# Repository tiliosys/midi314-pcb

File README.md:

midi@3:14 is a home-made electronic keyboard for playing music.

It has been designed with the following requirements:

* Small size, light weight.
* Uniform layout.
* Compatible with any computer hardware (PC, Raspberry Pi, &hellip;) and free software synthesizers.

As a result, midi@3:14 has the following characteristics:

* [Jankó](https://en.wikipedia.org/wiki/Jank%C3%B3_keyboard) layout with 3 rows of 14 keys.
* 5 potentiometers that can be used to change the volume, or any other control value supported by the MIDI standard.
* A USB-MIDI interface.

This repository contains the CAD files of the midi@3:14 keyboard PCB.
They have been initially created with Kicad 5, and migrated to Kicad 6.

Electronic design
-----------------

The keyboard is designed as a switch matrix using the same techniques as a typical mechanical computer keyboard.
The main components are:

* 42 switches from the Cherry MX family,
* 42 diodes to prevent the "ghosting" effect when playing chords,
* 5 potentiometers,
* A microcontroller module, the Arduino-compatible [SparkFun Pro Micro](https://www.sparkfun.com/products/12640),
* A custom printed circuit board (PCB).

For more explanations about making a matrix keyboard, see the blog post
[How to make a keyboard - The matrix](http://blog.komar.be/how-to-make-a-keyboard-the-matrix/)
by Michał Trybus.

In this project, while the actual keyboard is composed of 3 rows with 14 keys per row,
it is electrically organized as a 6&times;7 switch matrix:

PCB layout
----------

The PCB measures about 28.7 cm by 9.1 cm.
It uses two copper layers.
The switches, potentiometers, and the *Pro Micro* module are placed on the top layer; the diodes are placed on the bottom layer.

The following footprints are used:

* Potentiometers: Bourns PTV09A, vertical.
* Switches: Cherry MX 1u, PCB-mounted.
* Diodes: DO-35, horizontal, through-hole, 10.16 mm.
* Pro Micro: DIP-24, width 15.24 mm.

Here is a picture of the PCB, manufactured by a Chinese company called [Elecrow](https://www.elecrow.com).

Bill of materials and cost
--------------------------

Here is the list of parts used in this project, and the additional costs.
I have kept the prices in the currencies that were used when ordering (US dollars and Euros).
Note that these prices were applicable in March 2018.
They are likely to have changed since.

The first line shows that 50 key switches were ordered from WASD while only 42 were needed.
In fact, their unit price was lower when ordering 50 and it turned out to be cheaper.

| Description                                                                                                                 | Reference         | Provider                                                       | Qty | Unit price | Total price |
|:----------------------------------------------------------------------------------------------------------------------------|:------------------|:---------------------------------------------------------------|----:|-----------:|------------:|
| [Cherry MX Red Keyswitch (Linear) PCB Mounted](https://www.wasdkeyboards.com/cherry-mx-red-keyswitch-mx1a-l1nw-linear.html) | MX1A-L1NW         | [WASD](http://www.wasdkeyboards.com)                           |  50 |      $0.75 |      $37.50 |
| [Row 4, Size 1x1 Cherry MX Keycap](https://www.wasdkeyboards.com/row-4-size-1x1-cherry-mx-keycap.html), Beige               | R4-1X1            | [WASD](http://www.wasdkeyboards.com)                           |  23 |      $1.00 |      $23.00 |
| [Row 4, Size 1x1 Cherry MX Keycap](https://www.wasdkeyboards.com/row-4-size-1x1-cherry-mx-keycap.html), Charcoal            | R4-1X1            | [WASD](http://www.wasdkeyboards.com)                           |  18 |      $1.00 |      $18.00 |
| [Row 4, Size 1x1 Cherry MX Keycap](https://www.wasdkeyboards.com/row-4-size-1x1-cherry-mx-keycap.html), Orange              | R4-1X1            | [WASD](http://www.wasdkeyboards.com)                           |   1 |      $1.00 |       $1.00 |
| Keyboard parts, shipping to France                                                                                          |                   | USPS                                                           |   1 |     $23.50 |      $23.50 |
| Printed Circuit Board                                                                                                       |                   | [Elecrow](https://www.elecrow.com)                             |   1 |     $30.47 |      $30.47 |
| Printed Circuit Board, shipping to France                                                                                   |                   | DHL                                                            |   1 |     $20.03 |      $20.03 |
| Printed Circuit Board, customs                                                                                              |                   | DHL                                                            |   1 |    23.00 € |     23.00 € |
| Potentiometer, Bourns PTV09A series, 10 kOhm                                                                                | PTV09A-4225F-B103 | [Farnell](http://fr.farnell.com/)                              |   5 |     0.97 € |      4.85 € |
| Diodes                                                                                                                      | 1N4148            | [Farnell](http://fr.farnell.com/)                              |  50 |    0.682 € |      3.41 € |
| Components, shipping                                                                                                        |                   |                                                                |   1 |     6.90 € |      6.90 € |
| Components, VAT                                                                                                             |                   |                                                                |   1 |     3.44 € |      3.44 € |
| Leonardo Pro Micro ATmega32U4                                                                                               |                   | [Chip and love](https://www.chipandlove.ch)                    |   1 |    13.00 € |     13.00 € |
| Noise dampeners for Cherry MX switches                                                                                      |                   | [IT-Services irro](https://www.itservices-irro.de/) via Amazon | 120 |            |      7.99 € |
| Potentiometer knobs                                                                                                         |                   | [Electronic Loisirs](https://electronicloisirs.com/)           |   5 |          ? |           ? |

Known issues
------------

* The PCB has no mounting holes. They must be drilled manually.
* Potentiometers have been rotated by 180 degrees from their standard orientation.
  Bourns PTV09A potentiometers have a D-shaped shaft: you can use blank knobs, or knobs with a round hole and a set-screw.
* The spacing between potentiometers is too short.
  The knob diameter must be less than 19 mm.

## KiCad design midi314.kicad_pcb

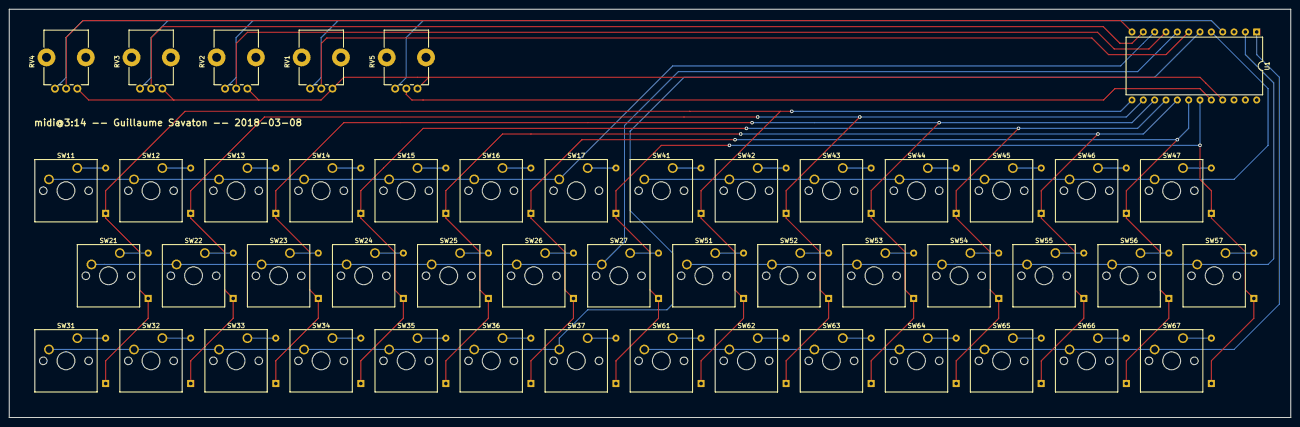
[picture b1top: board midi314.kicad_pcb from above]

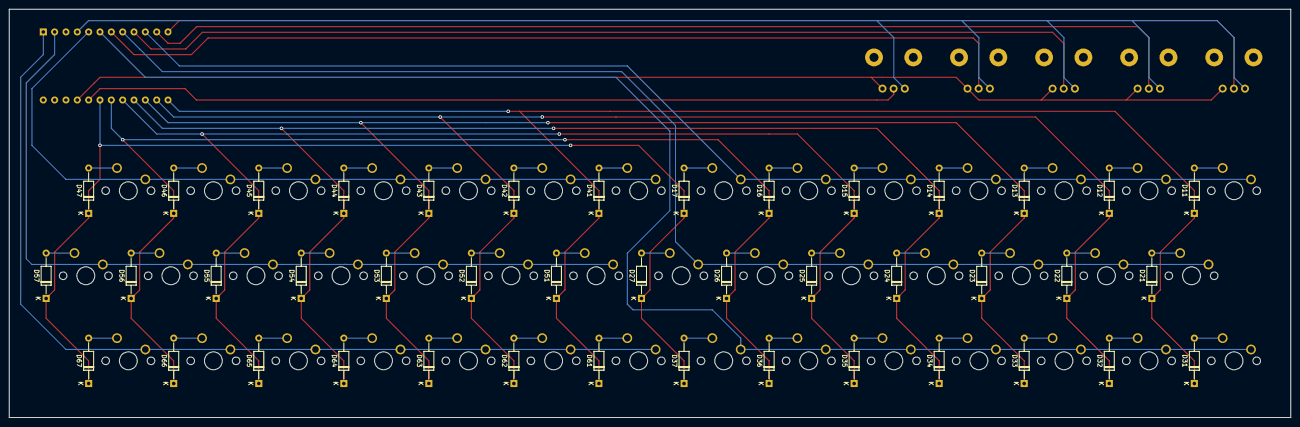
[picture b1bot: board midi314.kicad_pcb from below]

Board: 2 copper layers, 287.0 x 91.4 mm, 90 parts (42 on the bottom side), 62 nets.

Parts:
D11, D12, D13, D14, D15, D16, D17, D21, D22, D23, D24, D25, D26, D27, D31, D32, D33, D34, D35, D36, D37, D41, D42, D43, D44, D45, D46, D47, D51, D52, D53, D54, D55, D56, D57, D61, D62, D63, D64, D65, D66, D67: 1N4148; D_DO-35_SOD27_P10.16mm_Horizontal
RV1, RV2, RV3, RV4, RV5: POT; Potentiometer_Bourns_PTV09A-1_Single_Vertical
SW11, SW12, SW13, SW14, SW15, SW16, SW17, SW21, SW22, SW23, SW24, SW25, SW26, SW27, SW31, SW32, SW33, SW34, SW35, SW36, SW37, SW41, SW42, SW43, SW44, SW45, SW46, SW47, SW51, SW52, SW53, SW54, SW55, SW56, SW57, SW61, SW62, SW63, SW64, SW65, SW66, SW67: SW_Push; SW_Cherry_MX1A_1.00u_PCB
U1: Arduino_Pro_Micro; DIP-24_W15.24mm

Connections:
+5V: RV1.1, RV2.1, RV3.1, RV4.1, RV5.1, U1.21
COL1: D11.1, D21.1, D31.1, D41.1, D51.1, D61.1, U1.13
COL2: D12.1, D22.1, D32.1, D42.1, D52.1, D62.1, U1.14
COL3: D13.1, D23.1, D33.1, D43.1, D53.1, D63.1, U1.15
COL4: D14.1, D24.1, D34.1, D44.1, D54.1, D64.1, U1.16
COL5: D15.1, D25.1, D35.1, D45.1, D55.1, D65.1, U1.17
COL6: D16.1, D26.1, D36.1, D46.1, D56.1, D66.1, U1.18
COL7: D17.1, D27.1, D37.1, D47.1, D57.1, D67.1, U1.19
GND: RV1.3, RV2.3, RV3.3, RV4.3, RV5.3, U1.4
unnamed: D11.2, SW11.1
unnamed: D12.2, SW12.1
unnamed: D13.2, SW13.1
unnamed: D14.2, SW14.1
unnamed: D15.2, SW15.1
unnamed: D16.2, SW16.1
unnamed: D17.2, SW17.1
unnamed: D21.2, SW21.1
unnamed: D22.2, SW22.1
unnamed: D23.2, SW23.1
unnamed: D24.2, SW24.1
unnamed: D25.2, SW25.1
unnamed: D26.2, SW26.1
unnamed: D27.2, SW27.1
unnamed: D31.2, SW31.1
unnamed: D32.2, SW32.1
unnamed: D33.2, SW33.1
unnamed: D34.2, SW34.1
unnamed: D35.2, SW35.1
unnamed: D36.2, SW36.1
unnamed: D37.2, SW37.1
unnamed: D41.2, SW41.1
unnamed: D42.2, SW42.1
unnamed: D43.2, SW43.1
unnamed: D44.2, SW44.1
unnamed: D45.2, SW45.1
unnamed: D46.2, SW46.1
unnamed: D47.2, SW47.1
unnamed: D51.2, SW51.1
unnamed: D52.2, SW52.1
unnamed: D53.2, SW53.1
unnamed: D54.2, SW54.1
unnamed: D55.2, SW55.1
unnamed: D56.2, SW56.1
unnamed: D57.2, SW57.1
unnamed: D61.2, SW61.1
unnamed: D62.2, SW62.1
unnamed: D63.2, SW63.1
unnamed: D64.2, SW64.1
unnamed: D65.2, SW65.1
unnamed: D66.2, SW66.1
unnamed: D67.2, SW67.1
unnamed: RV1.2, U1.7
unnamed: RV2.2, U1.9
unnamed: RV3.2, U1.11
unnamed: RV4.2, U1.12
unnamed: RV5.2, U1.20
ROW1: SW11.2, SW12.2, SW13.2, SW14.2, SW15.2, SW16.2, SW17.2, U1.10
ROW2: SW21.2, SW22.2, SW23.2, SW24.2, SW25.2, SW26.2, SW27.2, U1.8
ROW3: SW31.2, SW32.2, SW33.2, SW34.2, SW35.2, SW36.2, SW37.2, U1.6
ROW4: SW41.2, SW42.2, SW43.2, SW44.2, SW45.2, SW46.2, SW47.2, U1.5
ROW5: SW51.2, SW52.2, SW53.2, SW54.2, SW55.2, SW56.2, SW57.2, U1.2
ROW6: SW61.2, SW62.2, SW63.2, SW64.2, SW65.2, SW66.2, SW67.2, U1.1

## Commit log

2022-07-03 Migrated from aumouvantsillage/midi314
2022-07-03 Migrated project to Kicad 6
2022-07-03 Removed obsolete .pro file
2022-07-03 Ignore backup dir
2022-07-03 Completed README
2022-07-05 README: formatting
